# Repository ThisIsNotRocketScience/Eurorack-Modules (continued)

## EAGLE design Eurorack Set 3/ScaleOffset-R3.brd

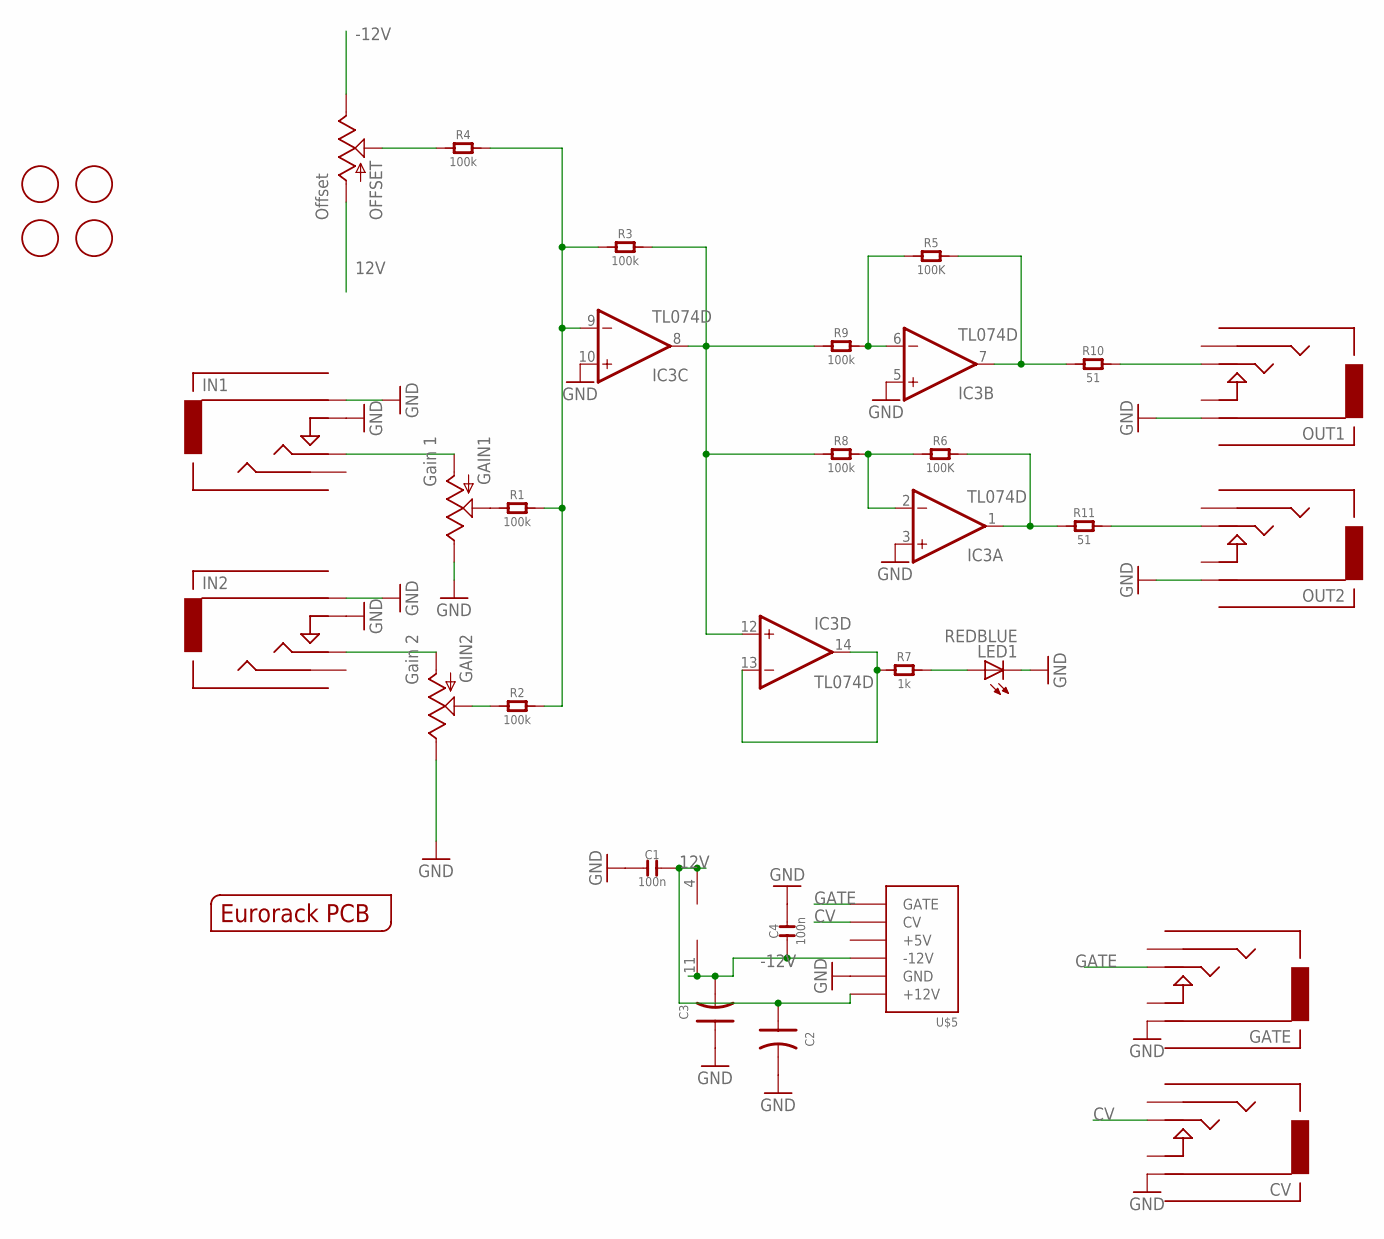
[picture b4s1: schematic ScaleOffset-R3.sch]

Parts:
C1, C4: 100n; C0603
C2, C3: C-POLAR-A; AVX-A
CV: CV; 3.5MM-JACK-SWITCH-13MM-OUTPUT
GAIN1: Gain 1; OG-POTS_ALPS_POT_VERTICAL
GAIN2: Gain 2; OG-POTS_ALPS_POT_VERTICAL
GATE: GATE; 3.5MM-JACK-SWITCH-13MM-OUTPUT
IC3: TL074D; SO14
IN1: Input 1; 3.5MM-JACK-SWITCH-13MM-INPUT
IN2: Input 2; 3.5MM-JACK-SWITCH-13MM-INPUT
LED1: REDBLUE; LED3MM
OFFSET: Offset; OG-POTS_ALPS_POT_VERTICAL
OUT1: 2; 3.5MM-JACK-SWITCH-13MM-OUTPUT
OUT2: 1; 3.5MM-JACK-SWITCH-13MM-OUTPUT
R1, R2, R3, R4, R8, R9: 100k; R0603
R5, R6: 100K; R0603
R7: 1k; R0603
R10, R11: 51; C0805
U$1, U$2, U$3, U$4: FIDUCIAL; FIDUCIAL_1MM
U$5: POWER; POWER_16
U$12: EURORACK_PCB6HP; EURORACK6HPPCB

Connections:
12V: C1.2, C2.+ (1), IC3.4 (V+), OFFSET.P$3 (A), U$5.9 (+12V), U$5.10 (+12V)
-12V: C3.- (2), C4.1, IC3.11 (V-), OFFSET.P$1 (E), U$5.1 (-12V), U$5.2 (-12V)
CV: CV.TIP@1 (TIP), CV.TIP@2 (TIP), U$5.13 (CV), U$5.14 (CV)
FBOUT1: IC3.7 (OUT), R5.2, R10.1
FBOUT2: IC3.1 (OUT), R6.2, R11.1
GATE: GATE.TIP@1 (TIP), GATE.TIP@2 (TIP), U$5.15 (GATE), U$5.16 (GATE)
GND: C1.1, C2.- (2), C3.+ (1), C4.2, CV.RING@1 (RING), CV.RING@2 (RING), GAIN1.P$1 (E), GAIN2.P$1 (E), GATE.RING@1 (RING), GATE.RING@2 (RING), IC3.3 (+IN), IC3.5 (+IN), IC3.10 (+IN), IN1.RING@1 (RING), IN1.RING@2 (RING), IN1.SWITCH@1 (SWITCH), IN1.SWITCH@2 (SWITCH), IN2.RING@1 (RING), IN2.RING@2 (RING), IN2.SWITCH@1 (SWITCH), IN2.SWITCH@2 (SWITCH), LED1.K (C), OUT1.RING@1 (RING), OUT1.RING@2 (RING), OUT2.RING@1 (RING), OUT2.RING@2 (RING), U$5.3 (GND), U$5.4 (GND), U$5.5 (GND), U$5.6 (GND), U$5.7 (GND), U$5.8 (GND)
unnamed: IC3.6 (-IN), R5.1, R9.2
unnamed: LED1.A, R7.2
unnamed: GAIN2.P$3 (A), IN2.TIP@1 (TIP), IN2.TIP@2 (TIP)
unnamed: GAIN1.P$3 (A), IN1.TIP@1 (TIP), IN1.TIP@2 (TIP)
unnamed: GAIN1.P$2 (S), R1.1
unnamed: GAIN2.P$2 (S), R2.1
unnamed: IC3.8 (OUT), IC3.12 (+IN), R3.2, R8.1, R9.1
unnamed: IC3.13 (-IN), IC3.14 (OUT), R7.1
unnamed: IC3.2 (-IN), R6.1, R8.2
OFFSET: OFFSET.P$2 (S), R4.1
OUT1: OUT1.TIP@1 (TIP), OUT1.TIP@2 (TIP), R10.2
OUT2: OUT2.TIP@1 (TIP), OUT2.TIP@2 (TIP), R11.2
SUMMING: IC3.9 (-IN), R1.2, R2.2, R3.1, R4.2

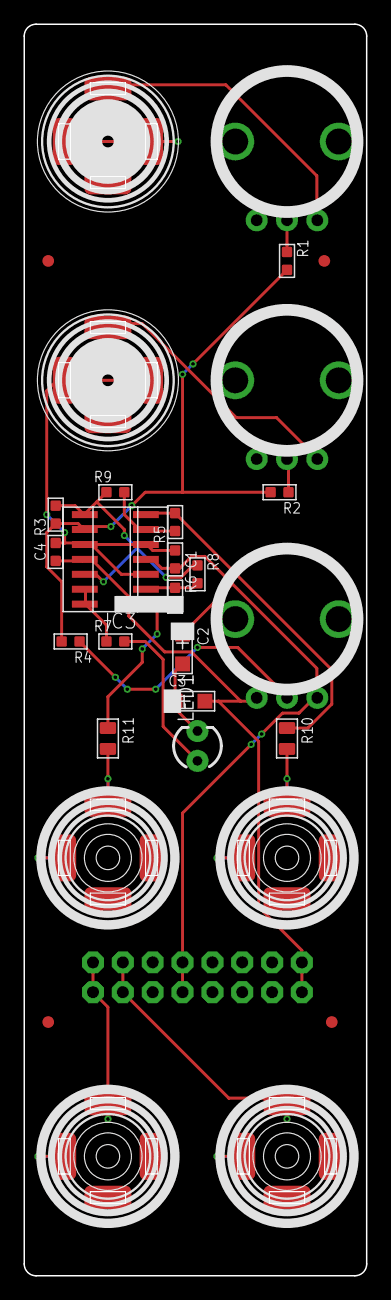
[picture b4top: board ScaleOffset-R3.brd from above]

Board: 2 copper layers, 29.1 x 106.5 mm, 32 parts (1 on the bottom side), 20 nets.

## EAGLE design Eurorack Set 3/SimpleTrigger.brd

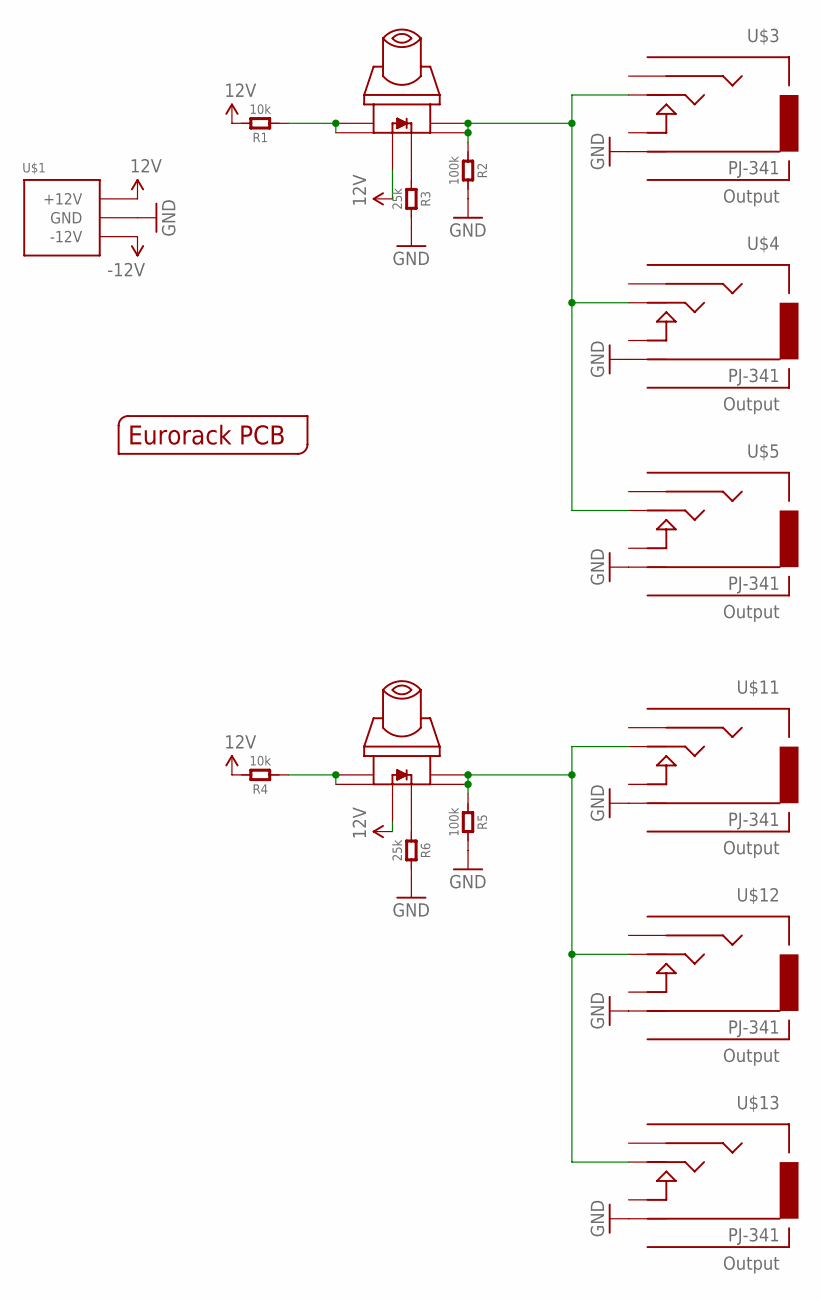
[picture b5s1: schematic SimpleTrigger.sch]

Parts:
R1, R4: 10k; R0603
R2, R5: 100k; R0603
R3, R6: 25k; R0603
U$1: POWER_SIMPLE10; POWER_10
U$2, U$10: SWITCH_W_LED_PB6149L-X-102WHITE; PB6149L
U$3, U$4, U$5, U$11, U$12, U$13: PJ-341; 3.5MM-JACK-SWITCH-13MM-OUTPUT
U$9: EURORACK_PCB2HP; EURORACK2HPPCB

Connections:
12V: R1.2, R4.2, U$1.9 (+12V), U$1.10 (+12V), U$2.LEDPOS (POS), U$10.LEDPOS (POS)
-12V: U$1.1 (-12V), U$1.2 (-12V)
GND: R2.2, R3.2, R5.2, R6.2, U$1.3 (GND), U$1.4 (GND), U$1.5 (GND), U$1.6 (GND), U$1.7 (GND), U$1.8 (GND), U$3.RING@3 (RING), U$4.RING@3 (RING), U$5.RING@3 (RING), U$11.RING@3 (RING), U$12.RING@3 (RING), U$13.RING@3 (RING)
unnamed: R3.1, U$2.LEDNEG (NEG)
unnamed: R1.1, U$2.1, U$2.2
unnamed: R2.1, U$2.3, U$2.4, U$3.TIP@3 (TIP), U$4.TIP@3 (TIP), U$5.TIP@3 (TIP)
unnamed: R6.1, U$10.LEDNEG (NEG)
unnamed: R4.1, U$10.1, U$10.2
unnamed: R5.1, U$10.3, U$10.4, U$11.TIP@3 (TIP), U$12.TIP@3 (TIP), U$13.TIP@3 (TIP)

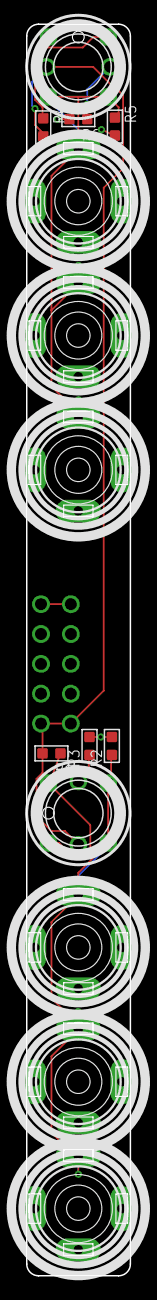
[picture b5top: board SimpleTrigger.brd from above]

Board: 2 copper layers, 8.8 x 106.5 mm, 16 parts (1 on the bottom side), 9 nets.

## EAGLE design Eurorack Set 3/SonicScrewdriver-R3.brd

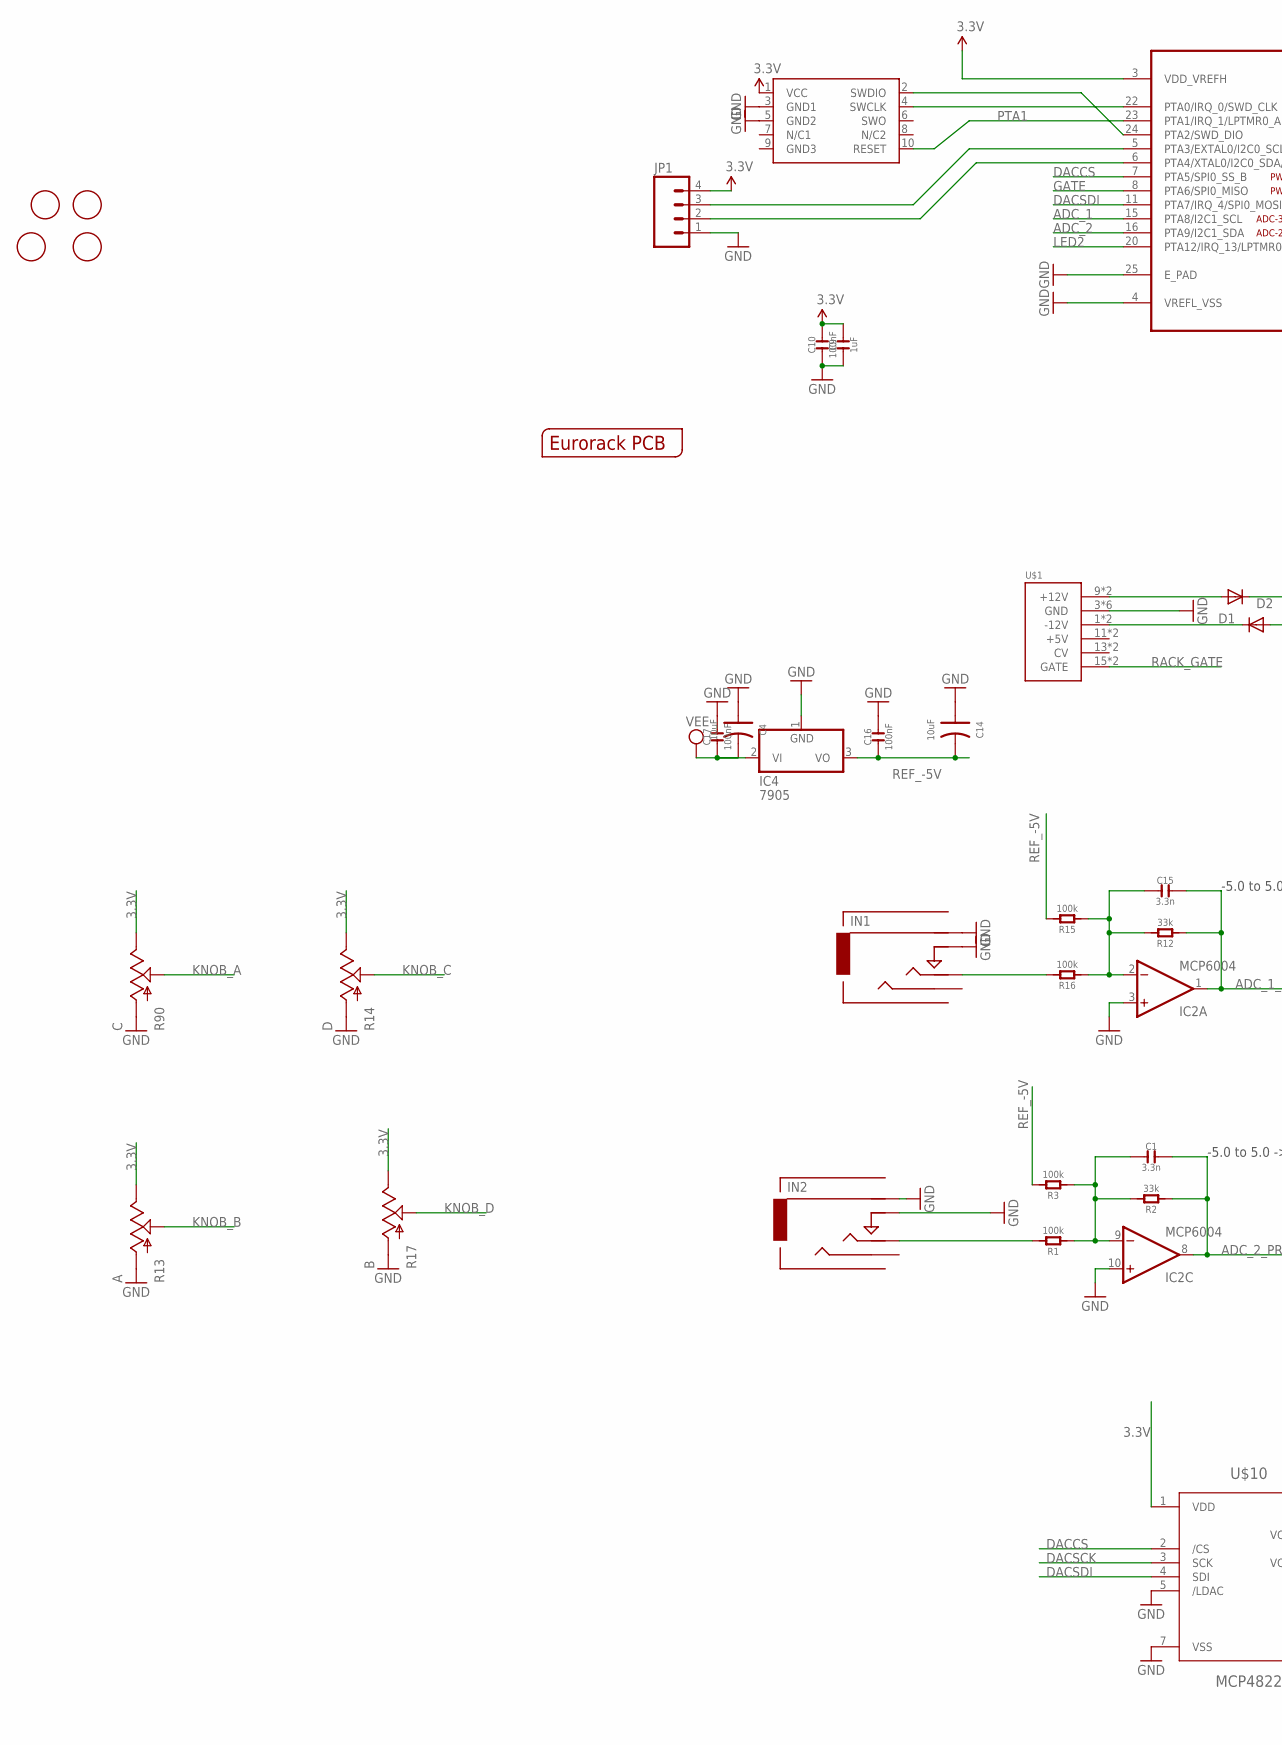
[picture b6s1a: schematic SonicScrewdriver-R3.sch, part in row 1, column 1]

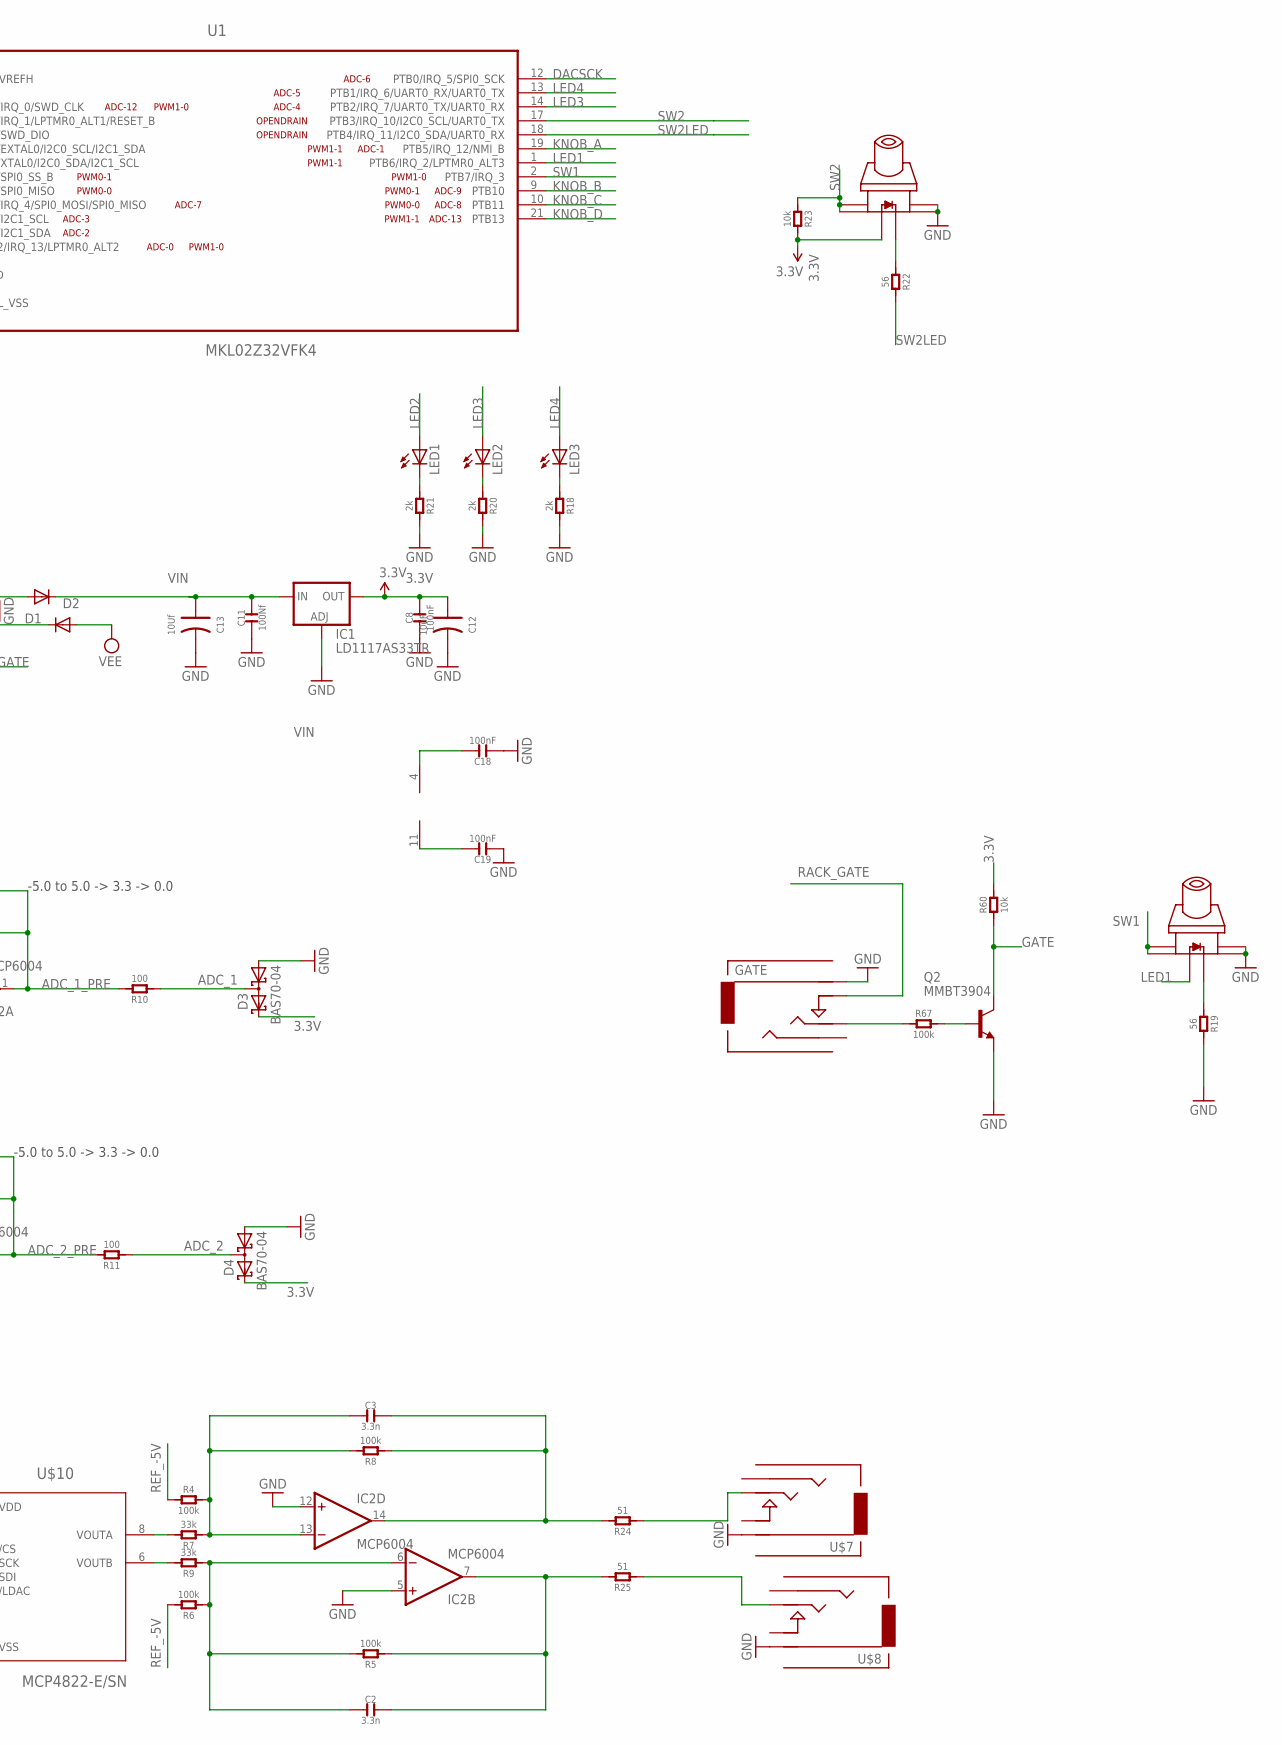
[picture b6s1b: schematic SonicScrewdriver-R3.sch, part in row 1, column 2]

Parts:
C1, C2, C3, C15: 3.3n; C0603
C4, C12, C14: 10uF; AVX-A
C8, C10, C16, C17, C18, C19: 100nF; C0603
C9: 1uF; C0603
C11: 100Nf; C0603
C13: 10Uf; AVX-A
D1, D2: 1N5819HW; SOD123
D3, D4: BAS70-04; SOT23
GATE: Gate; 3.5MM-JACK-SWITCH-13MM-INPUT
IC1: LD1117AS33TR; SOT223
IC2: MCP6004; SO14
IC4: 7905; TO220H
IN1: In 2; 3.5MM-JACK-SWITCH-13MM-INPUT
IN2: In 1; 3.5MM-JACK-SWITCH-13MM-INPUT
JP1: M04PTH; 1X04
LED1, LED2, LED3: LED3MM
Q2: MMBT3904; SOT23-BEC
R1, R3, R4, R5, R6, R8, R15, R16, R67: 100k; R0603
R2, R7, R9, R12: 33k; R0603
R10, R11: 100; R0603
R13: A; OG-POTS_ALPS_POT_VERTICAL
R14: D; OG-POTS_ALPS_POT_VERTICAL
R17: B; OG-POTS_ALPS_POT_VERTICAL
R18, R20, R21: 2k; R0603
R19, R22: 56; R0603
R23, R60: 10k; R0603
R24, R25: 51; R0603
R90: C; OG-POTS_ALPS_POT_VERTICAL
SWD1: CORTEX_SWD; M50-3600542
U1: MKL02Z32VFK4; QFN50P400X400X100-25N
U$1: POWER; POWER_16
U$2: EURORACK_PCB8HP; EURORACK8HPPCB
U$3, U$6: SWITCH_W_LED_PB6149L-X-102WHITE; PB6149L
U$4, U$5, U$9, U$11: FIDUCIAL; FIDUCIAL_1MM
U$7: Out 2; 3.5MM-JACK-SWITCH-13MM-OUTPUT
U$8: Out 1; 3.5MM-JACK-SWITCH-13MM-OUTPUT
U$10: MCP4822-E/SN; SOIC8-N_MC

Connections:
3.3V: C8.2, C9.2, C10.2, C12.+ (1), D3.2 (C2), D4.2 (C2), IC1.2 (OUT), IC1.4 (OUT), JP1.4, R13.P$1 (E), R14.P$1 (E), R17.P$1 (E), R23.2, R60.2, R90.P$1 (E), SWD1.1 (VCC), U1.3 (VDD_VREFH), U$3.LEDPOS (POS), U$10.1 (VDD)
ADC_1: D3.3 (C1A2), R10.1, U1.15 (PTA8/I2C1_SCL)
ADC_1_PRE: C15.2, IC2.1 (OUT), R10.2, R12.1
ADC_2: D4.3 (C1A2), R11.1, U1.16 (PTA9/I2C1_SDA)
ADC_2_PRE: C1.2, IC2.8 (OUT), R2.1, R11.2
DACCS: U1.7 (PTA5/SPI0_SS_B), U$10.2 (/CS)
DACSCK: U1.12 (PTB0/IRQ_5/SPI0_SCK), U$10.3 (SCK)
DACSDI: U1.11 (PTA7/IRQ_4/SPI0_MOSI/SPI0_MISO), U$10.4 (SDI)
GATE: Q2.C, R60.1, U1.8 (PTA6/SPI0_MISO)
GND: C4.+ (1), C8.1, C9.1, C10.1, C11.1, C12.- (2), C13.- (2), C14.+ (1), C16.2, C17.2, C18.1, C19.1, D3.1 (A1), D4.1 (A1), GATE.RING@1 (RING), GATE.RING@2 (RING), IC1.1 (ADJ), IC2.3 (+IN), IC2.5 (+IN), IC2.10 (+IN), IC2.12 (+IN), IC4.1 (GND), IN1.RING@1 (RING), IN1.RING@2 (RING), IN1.SWITCH@1 (SWITCH), IN1.SWITCH@2 (SWITCH), IN2.RING@1 (RING), IN2.RING@2 (RING), IN2.SWITCH@1 (SWITCH), IN2.SWITCH@2 (SWITCH), JP1.1, Q2.E, R13.P$3 (A), R14.P$3 (A), R17.P$3 (A), R18.2, R19.2, R20.2, R21.2, R90.P$3 (A), SWD1.3 (GND1), SWD1.5 (GND2), U1.4 (VREFL_VSS), U1.25 (E_PAD), U$1.3 (GND), U$1.4 (GND), U$1.5 (GND), U$1.6 (GND), U$1.7 (GND), U$1.8 (GND), U$3.3, U$3.4, U$6.3, U$6.4, U$7.RING@1 (RING), U$7.RING@2 (RING), U$8.RING@1 (RING), U$8.RING@2 (RING), U$10.5 (/LDAC), U$10.7 (VSS)
KNOB_A: R90.P$2 (S), U1.19 (PTB5/IRQ_12/NMI_B)
KNOB_B: R13.P$2 (S), U1.9 (PTB10)
KNOB_C: R14.P$2 (S), U1.10 (PTB11)
KNOB_D: R17.P$2 (S), U1.21 (PTB13)
LED1: U1.1 (PTB6/IRQ_2/LPTMR0_ALT3), U$6.LEDPOS (POS)
LED2: LED1.A, U1.20 (PTA12/IRQ_13/LPTMR0_ALT2)
LED3: LED2.A, U1.14 (PTB2/IRQ_7/UART0_TX/UART0_RX)
LED4: LED3.A, U1.13 (PTB1/IRQ_6/UART0_RX/UART0_TX)
unnamed: JP1.3, U1.5 (PTA3/EXTAL0/I2C0_SCL/I2C1_SDA)
unnamed: JP1.2, U1.6 (PTA4/XTAL0/I2C0_SDA/I2C1_SCL)
unnamed: IN1.TIP@1 (TIP), IN1.TIP@2 (TIP), R16.2
unnamed: C15.1, IC2.2 (-IN), R12.2, R15.1, R16.1
unnamed: SWD1.4 (SWCLK), U1.22 (PTA0/IRQ_0/SWD_CLK)
unnamed: IN2.TIP@1 (TIP), IN2.TIP@2 (TIP), R1.2
unnamed: SWD1.2 (SWDIO), U1.24 (PTA2/SWD_DIO)
unnamed: C1.1, IC2.9 (-IN), R1.1, R2.2, R3.1
unnamed: C2.1, IC2.6 (-IN), R5.2, R6.1, R9.1
unnamed: C3.1, IC2.13 (-IN), R4.2, R7.1, R8.2
unnamed: R7.2, U$10.8 (VOUTA)
unnamed: R9.2, U$10.6 (VOUTB)
unnamed: D1.A, U$1.9 (+12V), U$1.10 (+12V)
unnamed: R19.1, U$6.LEDNEG (NEG)
unnamed: LED3.K (C), R18.1
unnamed: LED2.K (C), R20.1
unnamed: LED1.K (C), R21.1
unnamed: C3.2, IC2.14 (OUT), R8.1, R24.2
unnamed: R22.1, U$3.LEDNEG (NEG)
unnamed: R25.1, U$8.TIP@1 (TIP), U$8.TIP@2 (TIP)
unnamed: R24.1, U$7.TIP@1 (TIP), U$7.TIP@2 (TIP)
unnamed: C2.2, IC2.7 (OUT), R5.1, R25.2
unnamed: GATE.TIP@1 (TIP), GATE.TIP@2 (TIP), R67.1
unnamed: D2.C, U$1.1 (-12V), U$1.2 (-12V)
unnamed: Q2.B, R67.2
PTA1: SWD1.10 (RESET), U1.23 (PTA1/IRQ_1/LPTMR0_ALT1/RESET_B)
RACK_GATE: GATE.SWITCH@1 (SWITCH), GATE.SWITCH@2 (SWITCH), U$1.15 (GATE), U$1.16 (GATE)
REF_-5V: C14.- (2), C16.1, IC4.3 (VO), R3.2, R4.1, R6.2, R15.2
SW1: U1.2 (PTB7/IRQ_3), U$6.1, U$6.2
SW2: R23.1, U1.17 (PTB3/IRQ_10/I2C0_SCL/UART0_TX), U$3.1, U$3.2
SW2LED: R22.2, U1.18 (PTB4/IRQ_11/I2C0_SDA/UART0_RX)
VEE: C4.- (2), C17.1, C19.2, D2.A, IC2.11 (V-), IC4.2 (VI)
VIN: C11.2, C13.+ (1), C18.2, D1.C, IC1.3 (IN), IC2.4 (V+)

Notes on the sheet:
-5.0 to 5.0 -> 3.3 -> 0.0

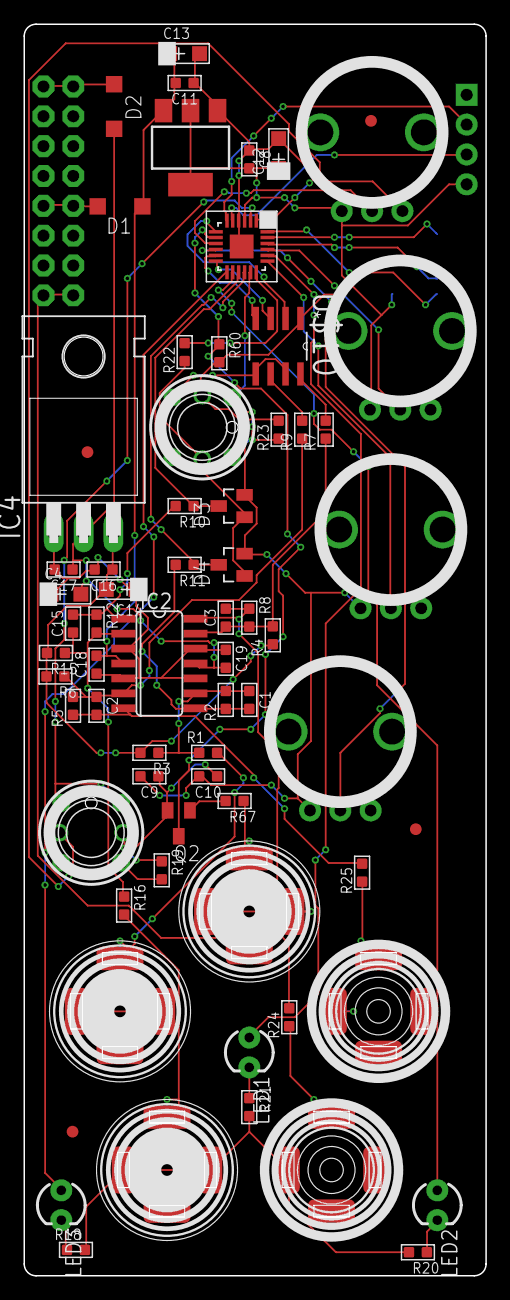
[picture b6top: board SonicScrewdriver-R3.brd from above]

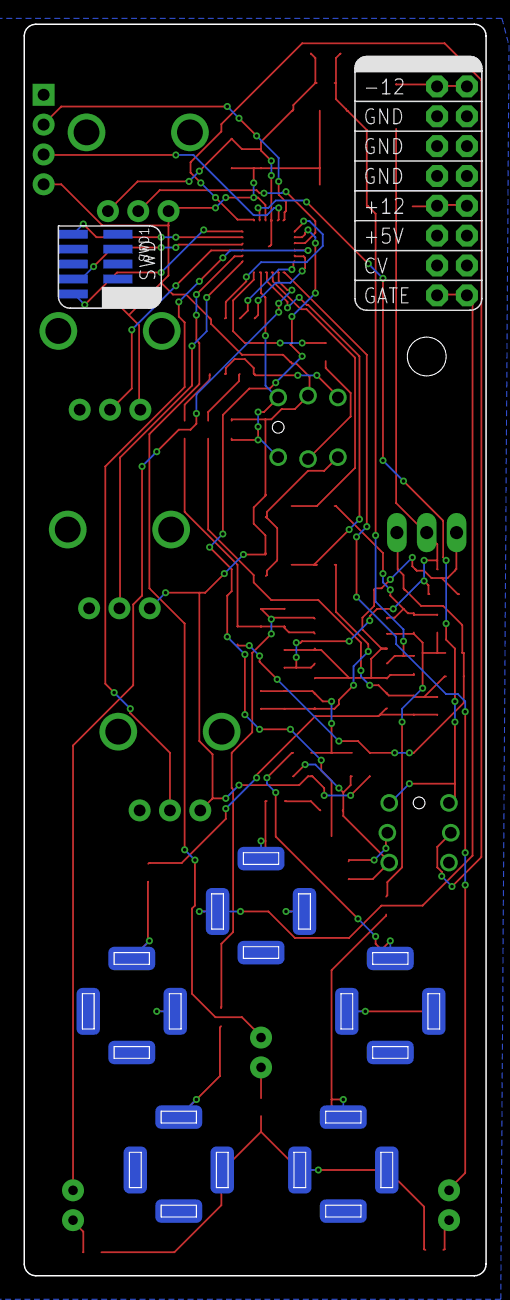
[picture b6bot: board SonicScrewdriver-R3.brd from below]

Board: 2 copper layers, 39.3 x 106.5 mm, 72 parts (2 on the bottom side), 51 nets.
